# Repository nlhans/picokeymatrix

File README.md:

## MIDI Key Matrix

Sources for a key matrix scanner based on Raspberry Pi Pico, with MIDI output, and 16-ch (analog) inputs with configurable pull-up/downs.

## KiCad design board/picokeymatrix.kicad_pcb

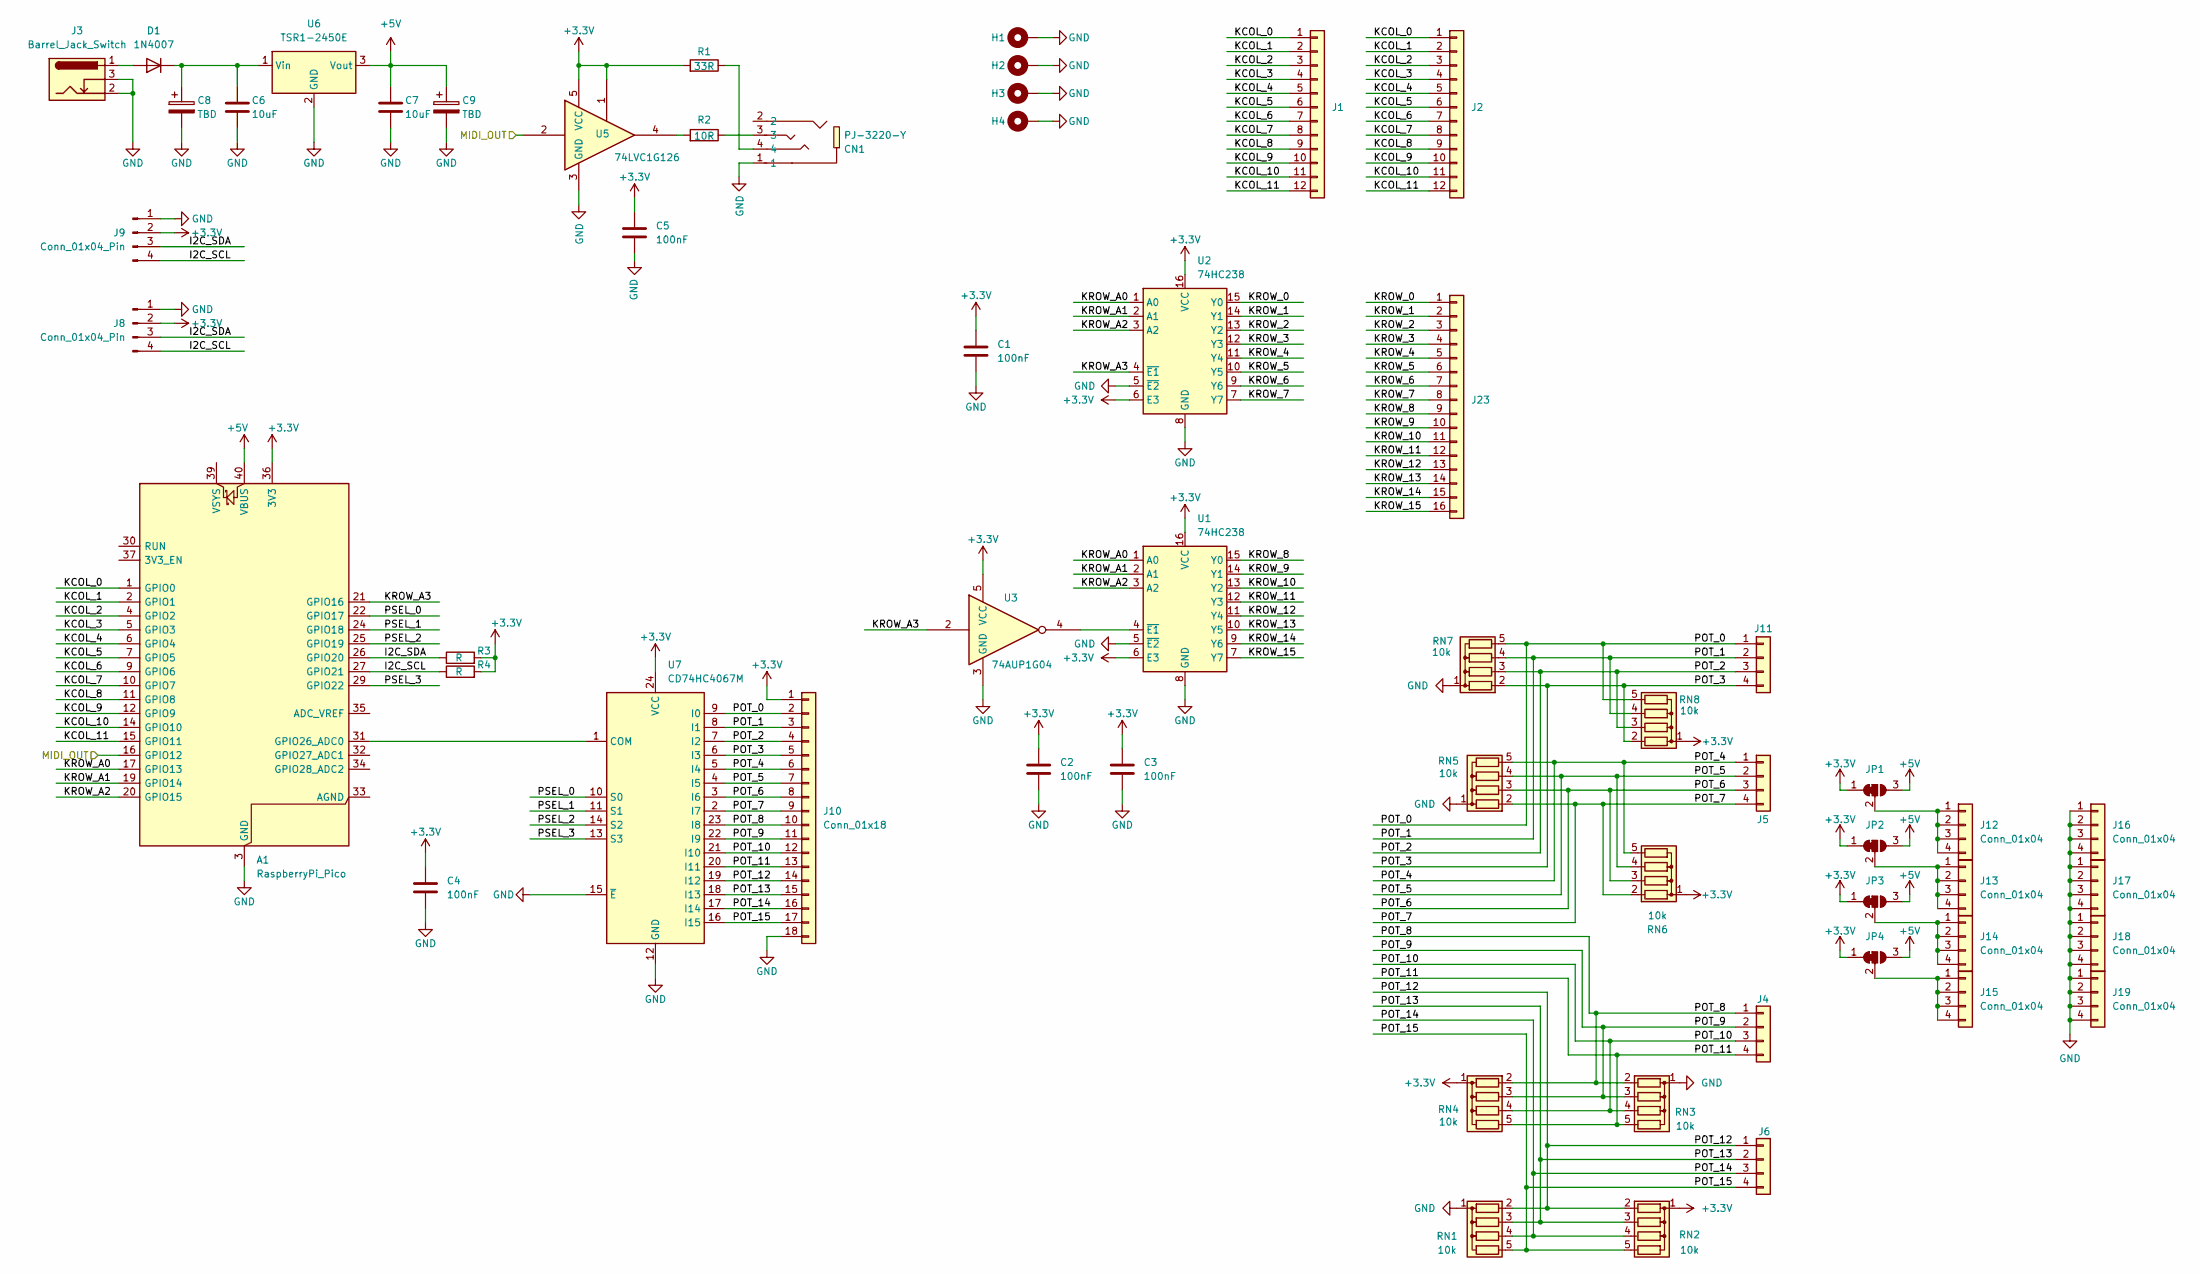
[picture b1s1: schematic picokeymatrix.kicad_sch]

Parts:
A1: RaspberryPi_Pico; RaspberryPi_Pico_Common_Unspecified
C1, C2, C3, C4, C5: 100nF; C_0603_1608Metric
C6, C7: 10uF; C_1206_3216Metric
C8, C9: TBD; C_Radial_D5.0mm_H7.0mm_P2.00mm
CN1: PJ-3220-Y; AUDIO-TH_PJ-3220-Y; LCSC Part C692442
D1: 1N4007; D_SMB
H1, H2, H3, H4: MountingHole_Pad; MountingHole_3.2mm_M3_Pad_Via
J1, J2: Conn_01x12; PinHeader_1x12_P2.54mm_Vertical
J3: Barrel_Jack_Switch; BarrelJack_Horizontal
J4, J5, J6, J11, J12, J13, J14, J15, J16, J17, J18, J19: Conn_01x04; PinHeader_1x04_P2.54mm_Vertical
J8, J9: Conn_01x04_Pin; NS-Tech_Grove_1x04_P2mm_Vertical
J10: Conn_01x18; PinHeader_1x18_P2.54mm_Vertical
J23: Conn_01x16; PinSocket_1x16_P2.54mm_Vertical
JP1, JP2, JP3, JP4: SolderJumper_3_Bridged12; SolderJumper-3_P1.3mm_Bridged12_RoundedPad1.0x1.5mm
R1: 33R; R_0603_1608Metric
R2: 10R; R_0603_1608Metric
R3, R4: R; R_0603_1608Metric
RN1, RN2, RN3, RN4, RN5, RN6, RN7, RN8: 10k; R_Array_SIP5
U1, U2: 74HC238; SOIC-16_3.9x9.9mm_P1.27mm
U3: 74AUP1G04; SOT-23-5
U5: 74LVC1G126; SOT-23-5; LCSC Part C7834
U6: TSR1-2450E; Converter_DCDC_TRACO_TSR1-xxxxE_THT
U7: CD74HC4067M; SOIC-24W_7.5x15.4mm_P1.27mm

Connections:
+3.3V: A1.36 (3V3), C1.1, C2.1, C3.1, C4.1, C5.1, J8.2, J9.2, J10.1, JP1.1 (A), JP2.1 (A), JP3.1 (A), JP4.1 (A), R1.2, R3.2, R4.2, RN2.1 (common), RN4.1 (common), RN6.1 (common), RN8.1 (common), U1.6 (E3), U1.16 (VCC), U2.6 (E3), U2.16 (VCC), U3.5 (VCC), U5.1, U5.5 (VCC), U7.24 (VCC)
+5V: A1.40 (VBUS), C7.1, C9.1, JP1.3 (B), JP2.3 (B), JP3.3 (B), JP4.3 (B), U6.3 (Vout)
/I2C_SCL: A1.27 (GPIO21), J8.4, J9.4, R4.1
/I2C_SDA: A1.26 (GPIO20), J8.3, J9.3, R3.1
/KCOL_0: A1.1 (GPIO0), J1.1, J2.1
/KCOL_1: A1.2 (GPIO1), J1.2, J2.2
/KCOL_2: A1.4 (GPIO2), J1.3, J2.3
/KCOL_3: A1.5 (GPIO3), J1.4, J2.4
/KCOL_4: A1.6 (GPIO4), J1.5, J2.5
/KCOL_5: A1.7 (GPIO5), J1.6, J2.6
/KCOL_6: A1.9 (GPIO6), J1.7, J2.7
/KCOL_7: A1.10 (GPIO7), J1.8, J2.8
/KCOL_8: A1.11 (GPIO8), J1.9, J2.9
/KCOL_9: A1.12 (GPIO9), J1.10, J2.10
/KCOL_10: A1.14 (GPIO10), J1.11, J2.11
/KCOL_11: A1.15 (GPIO11), J1.12, J2.12
/KROW_0: J23.1, U2.15 (Y0)
/KROW_1: J23.2, U2.14 (Y1)
/KROW_2: J23.3, U2.13 (Y2)
/KROW_3: J23.4, U2.12 (Y3)
/KROW_4: J23.5, U2.11 (Y4)
/KROW_5: J23.6, U2.10 (Y5)
/KROW_6: J23.7, U2.9 (Y6)
/KROW_7: J23.8, U2.7 (Y7)
/KROW_8: J23.9, U1.15 (Y0)
/KROW_9: J23.10, U1.14 (Y1)
/KROW_10: J23.11, U1.13 (Y2)
/KROW_11: J23.12, U1.12 (Y3)
/KROW_12: J23.13, U1.11 (Y4)
/KROW_13: J23.14, U1.10 (Y5)
/KROW_14: J23.15, U1.9 (Y6)
/KROW_15: J23.16, U1.7 (Y7)
/KROW_A0: A1.17 (GPIO13), U1.1 (A0), U2.1 (A0)
/KROW_A1: A1.19 (GPIO14), U1.2 (A1), U2.2 (A1)
/KROW_A2: A1.20 (GPIO15), U1.3 (A2), U2.3 (A2)
/KROW_A3: A1.21 (GPIO16), U2.4 (~E1), U3.2
/MIDI_OUT: A1.16 (GPIO12), U5.2
/POT_0: J10.2, J11.1, RN7.5 (R4), RN8.5 (R4), U7.9 (I0)
/POT_1: J10.3, J11.2, RN7.4 (R3), RN8.4 (R3), U7.8 (I1)
/POT_2: J10.4, J11.3, RN7.3 (R2), RN8.3 (R2), U7.7 (I2)
/POT_3: J10.5, J11.4, RN7.2 (R1), RN8.2 (R1), U7.6 (I3)
/POT_4: J5.1, J10.6, RN5.5 (R4), RN6.5 (R4), U7.5 (I4)
/POT_5: J5.2, J10.7, RN5.4 (R3), RN6.4 (R3), U7.4 (I5)
/POT_6: J5.3, J10.8, RN5.3 (R2), RN6.3 (R2), U7.3 (I6)
/POT_7: J5.4, J10.9, RN5.2 (R1), RN6.2 (R1), U7.2 (I7)
/POT_8: J4.1, J10.10, RN3.2 (R1), RN4.2 (R1), U7.23 (I8)
/POT_9: J4.2, J10.11, RN3.3 (R2), RN4.3 (R2), U7.22 (I9)
/POT_10: J4.3, J10.12, RN3.4 (R3), RN4.4 (R3), U7.21 (I10)
/POT_11: J4.4, J10.13, RN3.5 (R4), RN4.5 (R4), U7.20 (I11)
/POT_12: J6.1, J10.14, RN1.2 (R1), RN2.2 (R1), U7.19 (I12)
/POT_13: J6.2, J10.15, RN1.3 (R2), RN2.3 (R2), U7.18 (I13)
/POT_14: J6.3, J10.16, RN1.4 (R3), RN2.4 (R3), U7.17 (I14)
/POT_15: J6.4, J10.17, RN1.5 (R4), RN2.5 (R4), U7.16 (I15)
/PSEL_0: A1.22 (GPIO17), U7.10 (S0)
/PSEL_1: A1.24 (GPIO18), U7.11 (S1)
/PSEL_2: A1.25 (GPIO19), U7.14 (S2)
/PSEL_3: A1.29 (GPIO22), U7.13 (S3)
GND: A1.3 (GND), A1.8 (GND), A1.13 (GND), A1.18 (GND), A1.23 (GND), A1.28 (GND), A1.38 (GND), C1.2, C2.2, C3.2, C4.2, C5.2, C6.2, C7.2, C8.2, C9.2, CN1.1, H1.1, H2.1, H3.1, H4.1, J3.2, J3.3, J8.1, J9.1, J10.18, J16.1, J16.2, J16.3, J16.4, J17.1, J17.2, J17.3, J17.4, J18.1, J18.2, J18.3, J18.4, J19.1, J19.2, J19.3, J19.4, RN1.1 (common), RN3.1 (common), RN5.1 (common), RN7.1 (common), U1.5 (~E2), U1.8 (GND), U2.5 (~E2), U2.8 (GND), U3.3 (GND), U5.3 (GND), U6.2 (GND), U7.12 (GND), U7.15 (~E)
unnamed: A1.31 (GPIO26_ADC0), U7.1 (COM)
unnamed: CN1.3, R2.1
unnamed: CN1.4, R1.1
unnamed: D1.2 (A), J3.1
unnamed: C6.1, C8.1, D1.1 (K), U6.1 (Vin)
unnamed: J12.1, J12.2, J12.3, J12.4, JP1.2 (C)
unnamed: J13.1, J13.2, J13.3, J13.4, JP2.2 (C)
unnamed: J14.1, J14.2, J14.3, J14.4, JP3.2 (C)
unnamed: J15.1, J15.2, J15.3, J15.4, JP4.2 (C)
unnamed: R2.2, U5.4
unnamed: U1.4 (~E1), U3.4

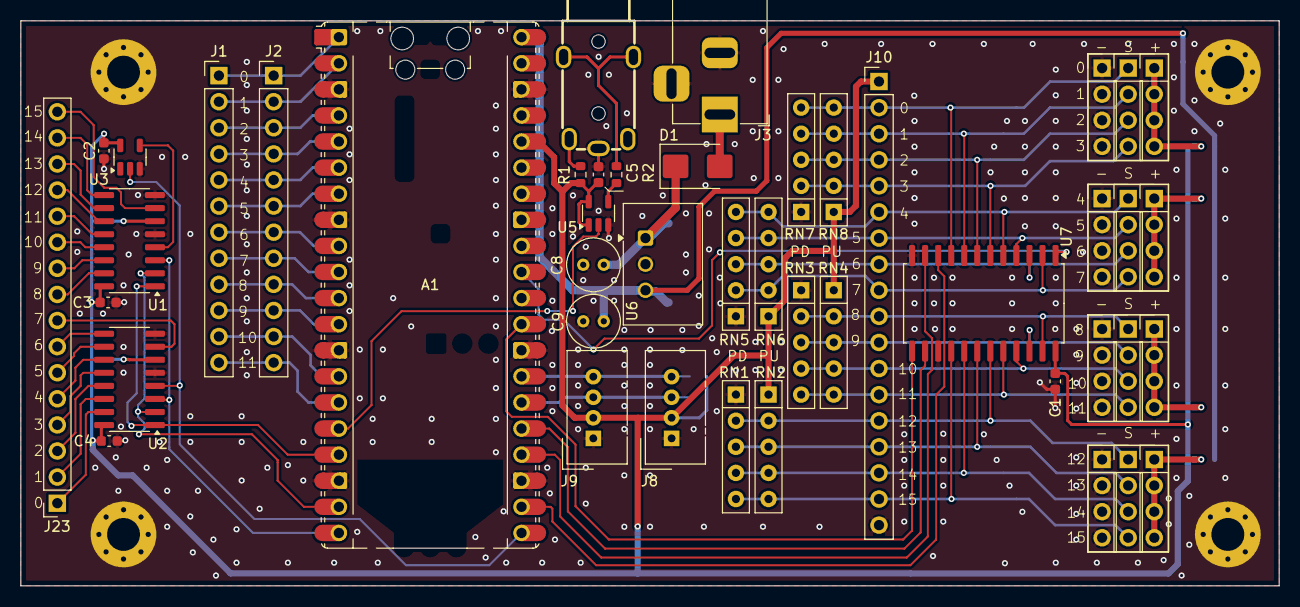
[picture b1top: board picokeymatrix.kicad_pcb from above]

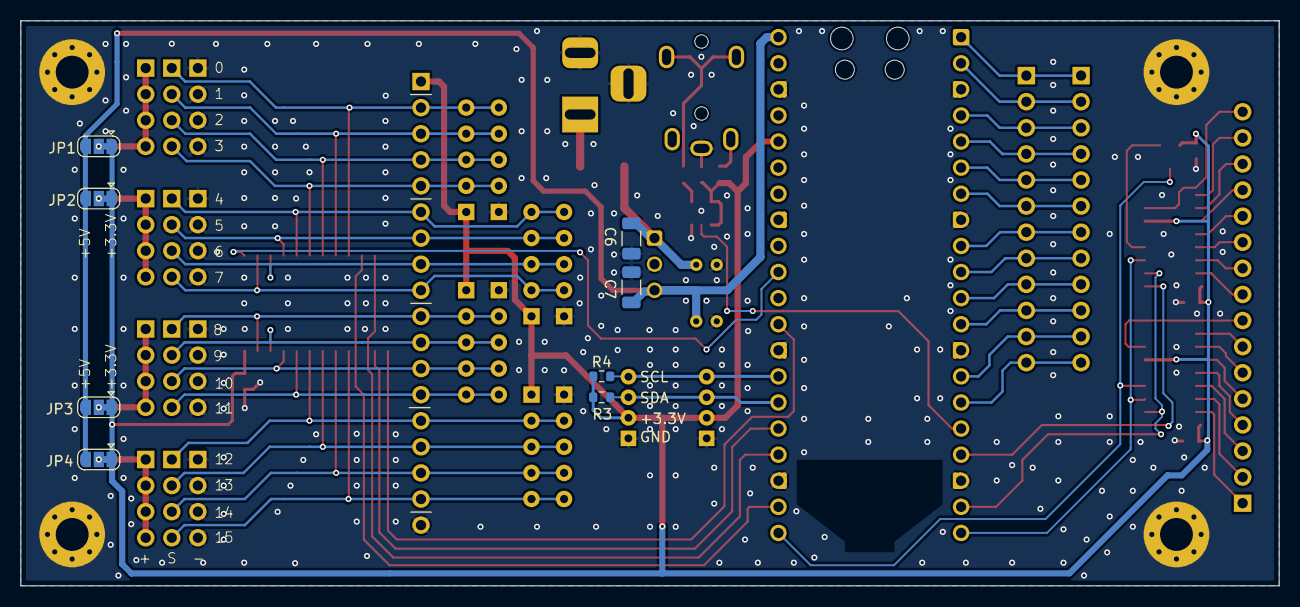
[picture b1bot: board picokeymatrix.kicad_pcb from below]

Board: 2 copper layers, 122.5 x 55.0 mm, 57 parts (8 on the bottom side), 69 nets.

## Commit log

2026-05-20 README
    Human annotation
2026-05-20 Design files
2026-05-22 Potmeter pinout, caps on supply
2026-05-29 Remove DS_Store
2026-05-29 Fix RPi pico footprint for TH mounting
2026-05-29 DS_Store
